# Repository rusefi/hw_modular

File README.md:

This repo is abandoned because https://github.com/andreika-git/hellen-one is the way!

Home of rusEFI modular prototyping hardware

https://github.com/rusefi/rusefi

Depends on libraries from https://github.com/rusefi/kicad-libraries

If you download complete repo do not forget to download libraries. If you git clone be sure to also

`git submodule update --init`

# Modules

[Nucleo 144 Wings Base Board](NUCLEO144_wing)

[TLE8888 Base Chip](TLE8888_Module)

[Protected Analog Inputs](Analog_Input_Module)

[6 channel Hi-Side Driver](highside_module)

[14 channel Low-Side Driver](lowside)

[TLE7209 H-Bridge](TLE7209_or_MC33186_H-Bridge_Breakout)

[Wideband Sense CJ125](cj125_Module)

# See also

[Forum thread](https://rusefi.com/forum/viewtopic.php?f=4&t=1459)

If you download complete repo do not forget to download libraries. If you git clone be sure to also

`git submodule update --init`

See [Manhattan Standard](Manhattan_standard.md)

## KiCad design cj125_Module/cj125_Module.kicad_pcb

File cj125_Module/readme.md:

See also https://github.com/rusefi/rusefi/wiki/WBO
 
[iBom](https://rusefi.com/docs/ibom/cj125_Module_latest.html)

on this board UR does NOT have build-in resistor divider

on this board UA resistor divider with 1.68 ratio

| Module Pin  | Sensor wire  |
|---|---|
| HT1  | H+ constant +12v  |
| GATE  | H- low side heater control  |
| VM1  |  VS/IP=VM=common virtual ground for VS and IP |
| IP1   | IP  |
| UN1  | VS pin 6, black  |
| IA1  |  CalR  pin 5, green |

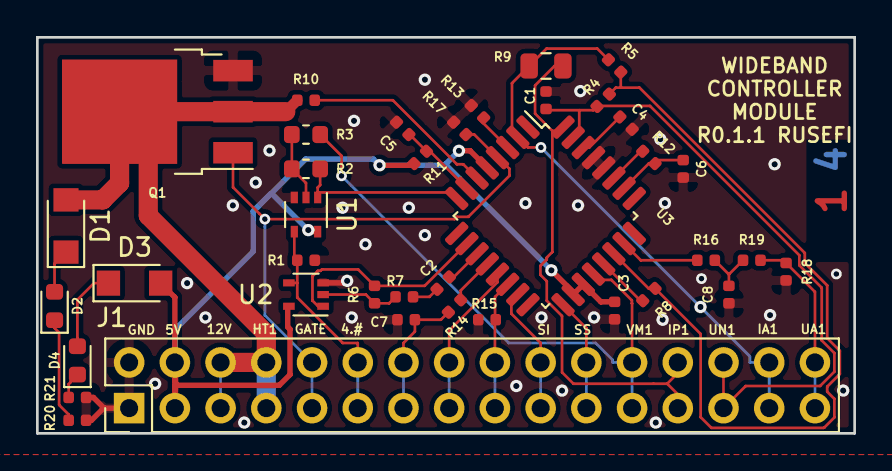
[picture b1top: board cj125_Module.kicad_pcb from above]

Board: 2 copper layers, 45.4 x 22.0 mm, 38 parts (0 on the bottom side), 36 nets.

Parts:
C1: 220pf; C_0402_1005Metric
C2, C6: 100nF; C_0402_1005Metric
C3, C4, C7, C8: 33nF; C_0402_1005Metric
C5: 1nF; C_0402_1005Metric
D1, D3: D_Schottky; D_SMF
D2, D4: LED; LED_0603_1608Metric
J1: Conn_02x20_Odd_Even; PinHeader_2x16_P2.54mm_Vertical
Q1: buk 100-50; TO-252-3_TabPin2
R1, R7: 10K; R_0402_1005Metric
R2: 220R; R_0603_1608Metric
R3: 82.5R; R_0603_1608Metric
R4, R12, R15: 100K; R_0402_1005Metric
R5: 470K; R_0402_1005Metric
R6: 21.6K; R_0402_1005Metric
R8, R20: 4.7K; R_0402_1005Metric
R9: 61.9R; R_0805_2012Metric
R10, R19: 6.8K; R_0402_1005Metric
R11, R13, R17, R18: 10k; R_0402_1005Metric
R14, R16, R21: 1K; R_0402_1005Metric
U1, U2: TS5A3166DCKR; SOT-353_SC-70-5
U3: CJ125; LQFP-32_7x7mm_P0.8mm

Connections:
/4.2_4.9: J1.11, J1.12, R1.2, U1.4, U2.4
/5V: C3.2, D3.2, J1.3, J1.4, R11.2, U1.5, U2.5, U3.5, U3.18, U3.19
/CJ125-1-SCK: J1.15, J1.16, U3.13
/CJ125-1-SI: J1.19, J1.20, U3.15
/CJ125-1-SO: J1.17, J1.18, R15.2, U3.14
/CJ125-1-SS: J1.21, J1.22, U3.17
/CJ125-UA-1: J1.31, J1.32, R18.1, R19.1
/CJ125_HEATER-1: D1.2, J1.5, J1.6, J1.7, J1.8, Q1.2, R10.1
/CJ125_UR-1: C7.1, J1.13, J1.14, R14.1
/COM: R2.1, R3.2, U1.2
/LSU-HEAT-GATE: J1.9, J1.10, Q1.1, R17.2, U3.4
/LSUIA1: J1.29, J1.30, R5.1, R9.1, U3.2
/LSUIP1: J1.25, J1.26, R9.2, U3.32
/LSUUN1: C1.1, J1.27, J1.28, R4.2, U3.31
/LSUVM1: J1.23, J1.24, R3.1, U3.20
/NO: R2.2, U1.1, U3.8
/WO2-12V: C4.2, U3.30
GND: C1.2, C3.1, C4.1, C5.2, C6.1, C7.2, C8.1, J1.1, J1.2, Q1.3, R1.1, R13.1, R15.1, R17.1, R18.2, R20.1, R21.1, U1.3, U2.3, U3.28, U3.29
unnamed: C2.1, R7.1
unnamed: C2.2, U3.11
unnamed: C5.1, R11.1, U3.7
unnamed: C6.2, R12.2, U3.26
unnamed: C8.2, R16.1, R19.2
unnamed: D1.1, D2.2
unnamed: D2.1, R20.2
unnamed: D3.1, D4.2
unnamed: D4.1, R21.2
unnamed: R4.1, R5.2, R8.1, U3.22
unnamed: R6.1, R7.2, U2.2
unnamed: R6.2, U2.1, U3.10
unnamed: R8.2, U3.21
unnamed: R10.2, U3.6
unnamed: R12.1, U3.27
unnamed: R13.2, U3.3
unnamed: R14.2, U3.12
unnamed: R16.2, U3.23

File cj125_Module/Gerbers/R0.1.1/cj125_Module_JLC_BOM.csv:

Comment,Designator,Footprint,LCSC, LCSC, Part #
"220pf","C1","Capacitor_SMD:C_0402_1005Metric","","C1530","C1530"
"33nF","C4,C7,C8,C3","Capacitor_SMD:C_0402_1005Metric",""," C1585"," C1585"
"1nF","C5","Capacitor_SMD:C_0402_1005Metric",""," C1523"," C1523"
"100nF","C6,C2","Capacitor_SMD:C_0402_1005Metric","","C1525","C1525"
"D_Schottky","D1,D3","Diode_SMD:D_SMF","","C64898",""
"LED","D2,D4","LED_SMD:LED_0603_1608Metric","","C2286",""
"Conn_02x20_Odd_Even","J1","Connector_PinHeader_2.54mm:PinHeader_2x16_P2.54mm_Vertical",""
"buk 100-50","Q1","Package_TO_SOT_SMD:TO-252-3_TabPin2","","","512-RFD16N05LSM9A"
"6.8K","R10,R19","Resistor_SMD:R_0402_1005Metric","","C25917","C25917"
"10k","R11,R13,R17,R18","Resistor_SMD:R_0402_1005Metric","","C25744","C25744"
"100K","R12,R4,R15","Resistor_SMD:R_0402_1005Metric","","C25741","C25741"
"1K","R16,R14,R21","Resistor_SMD:R_0402_1005Metric","","C11702","C11702"
"220R","R2","Resistor_SMD:R_0603_1608Metric",""," C22962"," C22962"
"82.5R","R3","Resistor_SMD:R_0603_1608Metric","","C23117",""
"470K","R5","Resistor_SMD:R_0402_1005Metric","","C25790","C25790"
"21.6K","R6","Resistor_SMD:R_0402_1005Metric",""," C25872"," C22962"
"10K","R7,R1","Resistor_SMD:R_0402_1005Metric",""," C25744",""
"4.7K","R8,R20","Resistor_SMD:R_0402_1005Metric","","C25900","C25900"
"61.9R","R9","Resistor_SMD:R_0805_2012Metric","","C17778","C17778"
"TS5A3166DCKR","U1,U2","Package_TO_SOT_SMD:SOT-353_SC-70-5",""
"CJ125","U3","Package_QFP:LQFP-32_7x7mm_P0.8mm",""

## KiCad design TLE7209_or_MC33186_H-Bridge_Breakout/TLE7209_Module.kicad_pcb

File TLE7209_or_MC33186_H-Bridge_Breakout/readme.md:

22x43mm

[Forum Thread](https://rusefi.com/forum/viewtopic.php?f=4&t=1521)

2 layer (also 4 layer version? TODO: add some clarity)

iBom https://rusefi.com/docs/ibom/TLE7209_Module_latest.html

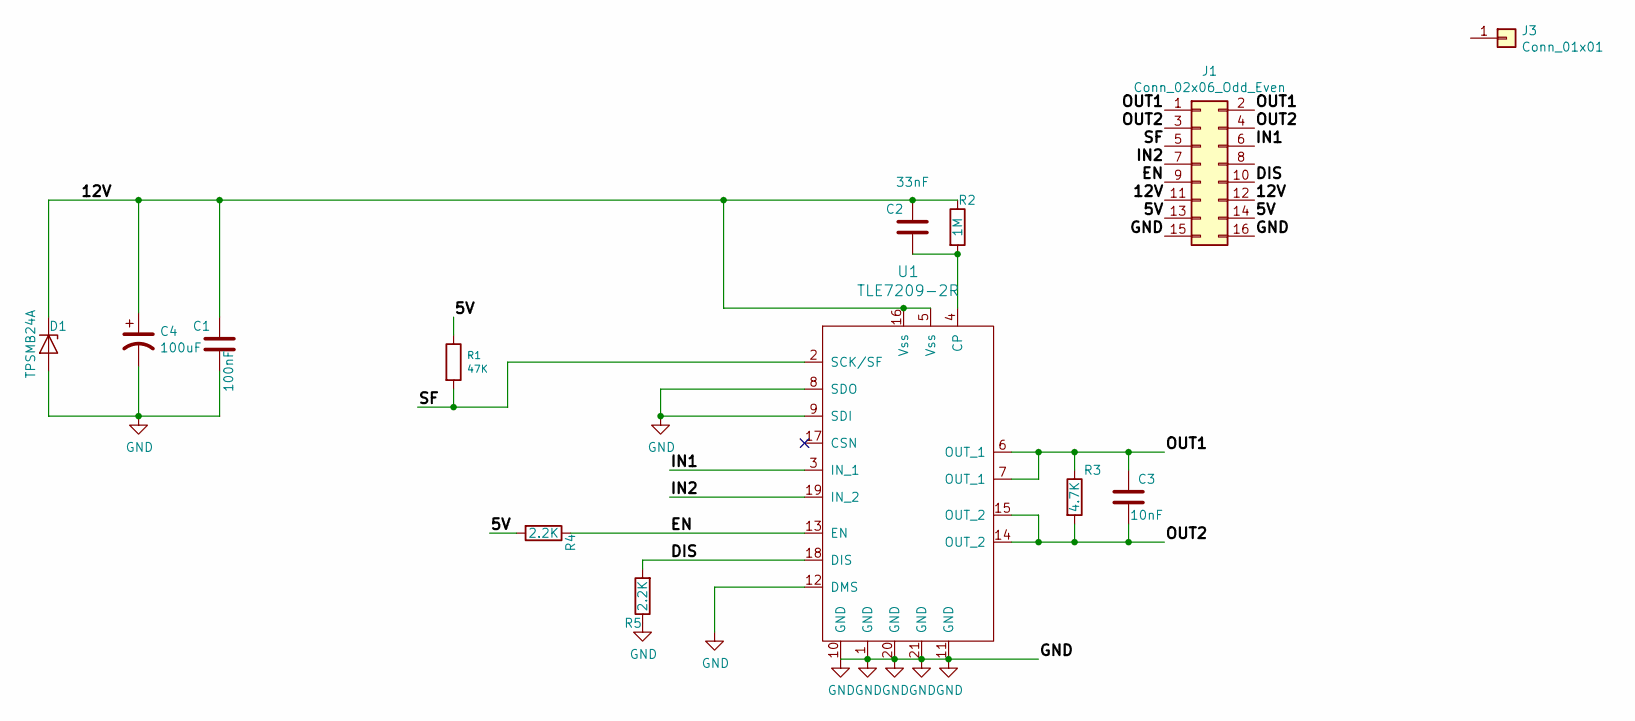
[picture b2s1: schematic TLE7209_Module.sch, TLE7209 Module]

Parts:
C1: 100nF; C_0805_2012Metric_Pad1.15x1.40mm_HandSolder
C2: 33nF; C_0805_2012Metric_Pad1.15x1.40mm_HandSolder
C3: 10nF; C_0805_2012Metric_Pad1.15x1.40mm_HandSolder
C4: 100uF; CP_Elec_8x10
D1: TPSMB24A; D_SMA
J1: Conn_02x06_Odd_Even; PinHeader_2x08_P2.54mm_Vertical
J3: Conn_01x01; 1pin
R1: 47K; R_0805_2012Metric_Pad1.15x1.40mm_HandSolder
R2: 1M; R_0805_2012Metric_Pad1.15x1.40mm_HandSolder
R3: 4.7K; R_0805_2012Metric_Pad1.15x1.40mm_HandSolder
R4, R5: 2.2K; R_0805_2012Metric_Pad1.15x1.40mm_HandSolder
U1: TLE7209-2R; HSOP-20-1EP_11.0x15.9mm_P1.27mm_SlugDown_ThermalVias

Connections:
/5V: J1.13, J1.14, R1.1, R4.2
/12V: C1.1, C2.1, C4.1, D1.1 (K), J1.11, J1.12, R2.1, U1.5 (Vss), U1.16 (Vss)
/DIS: J1.10, R5.2, U1.18 (DIS)
/EN: J1.9, R4.1, U1.13 (EN)
/IN1: J1.6, U1.3 (IN_1)
/IN2: J1.7, U1.19 (IN_2)
/OUT1: C3.1, J1.1, J1.2, R3.1, U1.6 (OUT_1), U1.7 (OUT_1)
/OUT2: C3.2, J1.3, J1.4, R3.2, U1.14 (OUT_2), U1.15 (OUT_2)
/SF: J1.5, R1.2, U1.2 (SCK/SF)
GND: C1.2, C4.2, D1.2 (A), J1.15, J1.16, R5.1, U1.1 (GND), U1.8 (SDO), U1.9 (SDI), U1.10 (GND), U1.11 (GND), U1.12 (DMS), U1.20 (GND), U1.21 (GND)
unnamed: C2.2, R2.2, U1.4 (CP)

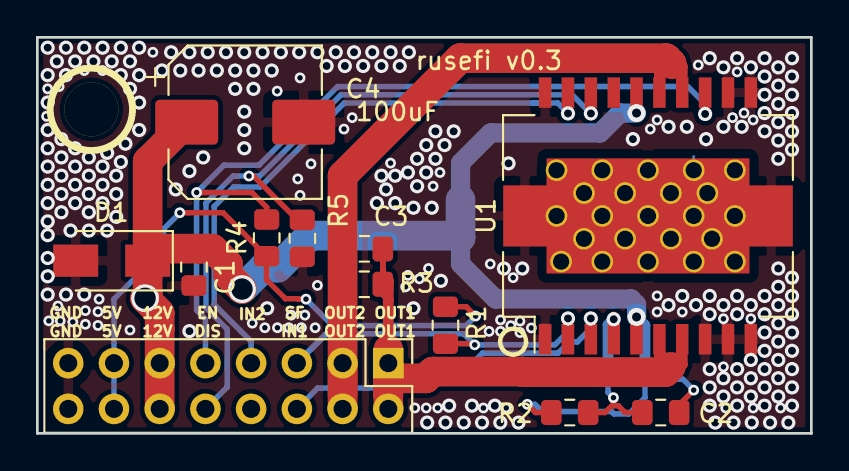
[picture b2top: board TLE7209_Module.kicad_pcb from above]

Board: 2 copper layers, 43.0 x 22.0 mm, 13 parts (0 on the bottom side), 11 nets.

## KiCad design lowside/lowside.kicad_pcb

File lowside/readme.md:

[iBOM](https://rusefi.com/docs/ibom/lowside_0.1.html)

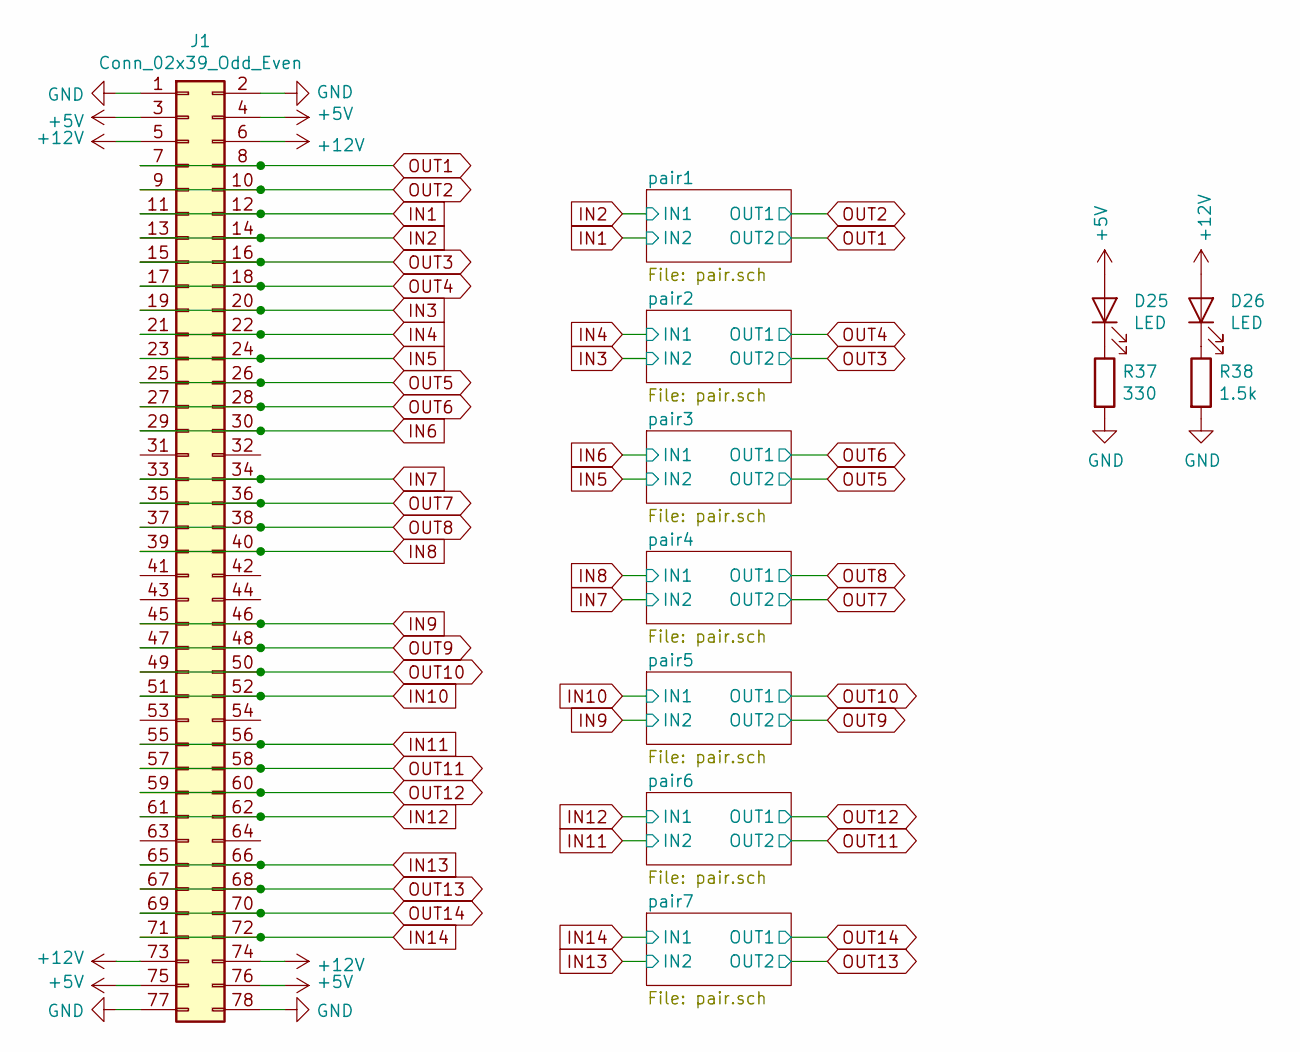
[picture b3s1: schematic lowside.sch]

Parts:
D25, D26: LED; LED_0603_1608Metric
J1: Conn_02x39_Odd_Even; PinHeader_2x39_P2.54mm_Vertical
R37: 330; R_0603_1608Metric
R38: 1.5k; R_0603_1608Metric

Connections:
+5V: D25.2 (A), J1.3, J1.4, J1.75, J1.76
+12V: D26.2 (A), J1.5, J1.6, J1.73, J1.74; also elsewhere on the board
GND: J1.1, J1.2, J1.77, J1.78, R37.2, R38.2; also elsewhere on the board
IN1: J1.11, J1.12; also elsewhere on the board
IN2: J1.13, J1.14; also elsewhere on the board
IN3: J1.19, J1.20; also elsewhere on the board
IN4: J1.21, J1.22; also elsewhere on the board
IN5: J1.23, J1.24; also elsewhere on the board
IN6: J1.29, J1.30; also elsewhere on the board
IN7: J1.33, J1.34; also elsewhere on the board
IN8: J1.39, J1.40; also elsewhere on the board
IN9: J1.45, J1.46; also elsewhere on the board
IN10: J1.51, J1.52; also elsewhere on the board
IN11: J1.55, J1.56; also elsewhere on the board
IN12: J1.61, J1.62; also elsewhere on the board
IN13: J1.65, J1.66; also elsewhere on the board
IN14: J1.71, J1.72; also elsewhere on the board
unnamed: D25.1 (K), R37.1
unnamed: D26.1 (K), R38.1
OUT3: J1.15, J1.16; also elsewhere on the board
OUT4: J1.17, J1.18; also elsewhere on the board
OUT5: J1.25, J1.26; also elsewhere on the board
OUT6: J1.27, J1.28; also elsewhere on the board
OUT9: J1.47, J1.48; also elsewhere on the board
OUT10: J1.49, J1.50; also elsewhere on the board
OUT11: J1.57, J1.58; also elsewhere on the board
OUT12: J1.59, J1.60; also elsewhere on the board
OUT13: J1.67, J1.68; also elsewhere on the board
OUT14: J1.69, J1.70; also elsewhere on the board

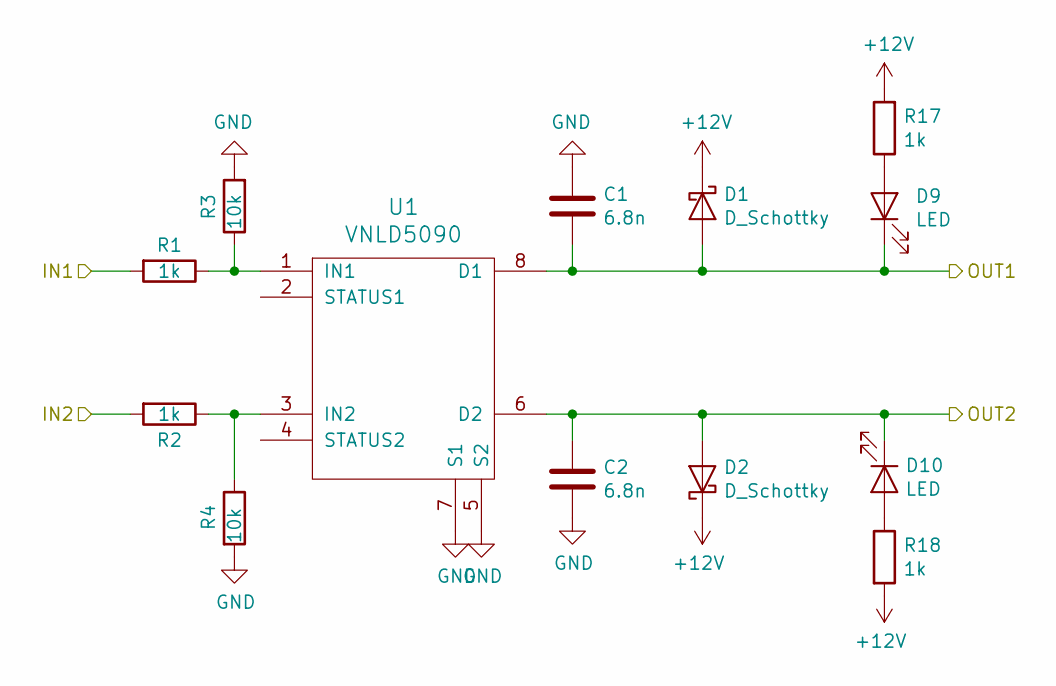
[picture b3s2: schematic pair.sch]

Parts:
C1, C2: 6.8n; C_0603_1608Metric
D1, D2: D_Schottky; D_SMF
D15, D16: LED; LED_0603_1608Metric
R1, R2, R23, R24: 1k; R_0603_1608Metric
R3, R4: 10k; R_0603_1608Metric
U1: VNLD5090; SO-8_3.9x4.9mm_P1.27mm

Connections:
+12V: D1.1 (K), D2.1 (K), R23.2, R24.2; also elsewhere on the board
GND: C1.2, C2.2, R3.2, R4.2, U1.5 (S2), U1.7 (S1); also elsewhere on the board
IN1: R2.2; also elsewhere on the board
IN2: R1.2; also elsewhere on the board
unnamed: D15.2 (A), R23.1
unnamed: D16.2 (A), R24.1
unnamed: R1.1, R3.1, U1.1 (IN1)
unnamed: R2.1, R4.1, U1.3 (IN2)

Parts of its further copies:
C3, C4, C5, C6, C7, C8, C9, C10, C11, C12, C13, C14: 6.8n; C_0603_1608Metric
D3, D4, D5, D6, D7, D8, D17, D18, D21, D22, D27, D28: D_Schottky; D_SMF
D9, D10, D11, D12, D13, D14, D19, D20, D23, D24, D29, D30: LED; LED_0603_1608Metric
R5, R6, R9, R10, R13, R14, R17, R18, R19, R20, R21, R22, R25, R26, R29, R30, R31, R32, R35, R36, R39, R40, R43, R44: 1k; R_0603_1608Metric
R7, R8, R11, R12, R15, R16, R27, R28, R33, R34, R41, R42: 10k; R_0603_1608Metric
U2, U3, U4, U5, U6, U7: VNLD5090; SO-8_3.9x4.9mm_P1.27mm

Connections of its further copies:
+12V: D3.1 (K), D4.1 (K), D5.1 (K), D6.1 (K), D7.1 (K), D8.1 (K), D17.1 (K), D18.1 (K), D21.1 (K), D22.1 (K), D27.1 (K), D28.1 (K), R17.2, R18.2, R19.2, R20.2, R21.2, R22.2, R29.2, R30.2, R35.2, R36.2, R43.2, R44.2; also elsewhere on the board
GND: C3.2, C4.2, C5.2, C6.2, C7.2, C8.2, C9.2, C10.2, C11.2, C12.2, C13.2, C14.2, R7.2, R8.2, R11.2, R12.2, R15.2, R16.2, R27.2, R28.2, R33.2, R34.2, R41.2, R42.2, U2.5 (S2), U2.7 (S1), U3.5 (S2), U3.7 (S1), U4.5 (S2), U4.7 (S1), U5.5 (S2), U5.7 (S1), U6.5 (S2), U6.7 (S1), U7.5 (S2), U7.7 (S1); also elsewhere on the board
IN3: R6.2; also elsewhere on the board
IN4: R5.2; also elsewhere on the board
IN5: R10.2; also elsewhere on the board
IN6: R9.2; also elsewhere on the board
IN7: R14.2; also elsewhere on the board
IN8: R13.2; also elsewhere on the board
IN9: R26.2; also elsewhere on the board
IN10: R25.2; also elsewhere on the board
IN11: R32.2; also elsewhere on the board
IN12: R31.2; also elsewhere on the board
IN13: R40.2; also elsewhere on the board
IN14: R39.2; also elsewhere on the board
unnamed: D9.2 (A), R17.1
unnamed: D10.2 (A), R18.1
unnamed: D11.2 (A), R19.1
unnamed: D12.2 (A), R20.1
unnamed: D13.2 (A), R21.1
unnamed: D14.2 (A), R22.1
unnamed: D19.2 (A), R29.1
unnamed: D20.2 (A), R30.1
unnamed: D23.2 (A), R35.1
unnamed: D24.2 (A), R36.1
unnamed: D29.2 (A), R43.1
unnamed: D30.2 (A), R44.1
unnamed: R5.1, R7.1, U2.1 (IN1)
unnamed: R6.1, R8.1, U2.3 (IN2)
unnamed: R10.1, R12.1, U3.3 (IN2)
unnamed: R9.1, R11.1, U3.1 (IN1)
unnamed: R13.1, R15.1, U4.1 (IN1)
unnamed: R14.1, R16.1, U4.3 (IN2)
unnamed: R25.1, R27.1, U5.1 (IN1)
unnamed: R26.1, R28.1, U5.3 (IN2)
unnamed: R31.1, R33.1, U6.1 (IN1)
unnamed: R32.1, R34.1, U6.3 (IN2)
unnamed: R39.1, R41.1, U7.1 (IN1)
unnamed: R40.1, R42.1, U7.3 (IN2)
OUT3: C4.1, D4.2 (A), D12.1 (K), U2.6 (D2); also elsewhere on the board
OUT4: C3.1, D3.2 (A), D11.1 (K), U2.8 (D1); also elsewhere on the board
OUT5: C6.1, D6.2 (A), D14.1 (K), U3.6 (D2); also elsewhere on the board
OUT6: C5.1, D5.2 (A), D13.1 (K), U3.8 (D1); also elsewhere on the board
OUT9: C10.1, D18.2 (A), D20.1 (K), U5.6 (D2); also elsewhere on the board
OUT10: C9.1, D17.2 (A), D19.1 (K), U5.8 (D1); also elsewhere on the board
OUT11: C12.1, D22.2 (A), D24.1 (K), U6.6 (D2); also elsewhere on the board
OUT12: C11.1, D21.2 (A), D23.1 (K), U6.8 (D1); also elsewhere on the board
OUT13: C14.1, D28.2 (A), D30.1 (K), U7.6 (D2); also elsewhere on the board
OUT14: C13.1, D27.2 (A), D29.1 (K), U7.8 (D1); also elsewhere on the board

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
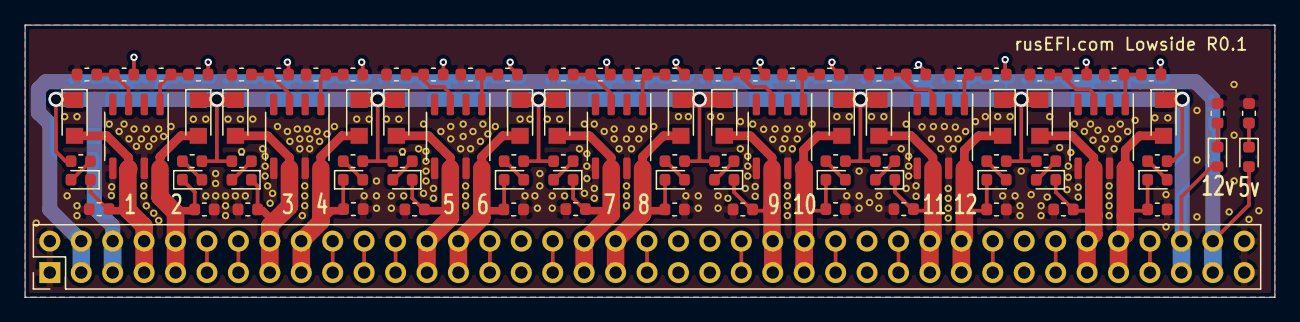
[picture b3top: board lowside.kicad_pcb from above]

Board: 4 copper layers, 101.0 x 22.0 mm, 96 parts (0 on the bottom side), 61 nets.

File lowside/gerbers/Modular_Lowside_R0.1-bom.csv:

Comment,Designator,Footprint,LCSC Part #
"6.8n",C1 C2 C3 C4 C5 C6 C7 C8 C9 C10 C11 C12 C13 C14 ,"Capacitor_SMD:C_0603_1608Metric","C1631"
"D_Schottky",D1 D2 D3 D4 D5 D6 D7 D8 D17 D18 D21 D22 D27 D28 ,"Diode_SMD:D_SMF","C156309"
"LED",D25 D26 D10 D9 D12 D11 D14 D13 D16 D15 D20 D19 D24 D23 D30 D29 ,"LED_SMD:LED_0603_1608Metric","C2286"
"Conn_02x39_Odd_Even",J1 ,"Connector_PinHeader_2.54mm:PinHeader_2x39_P2.54mm_Vertical",
"1k",R1 R2 R18 R17 R5 R6 R20 R19 R9 R10 R22 R21 R13 R14 R24 R23 R25 R26 R30 R29 R31 R32 R36 R35 R39 R40 R44 R43 ,"Resistor_SMD:R_0603_1608Metric","C21190"
"330",R37 ,"Resistor_SMD:R_0603_1608Metric","C23025"
"1.5k",R38 ,"Resistor_SMD:R_0603_1608Metric","C25867"
"10k",R4 R3 R8 R7 R12 R11 R16 R15 R28 R27 R34 R33 R42 R41 ,"Resistor_SMD:R_0603_1608Metric","C25804"
"VNLD5090",U1 U2 U3 U4 U5 U6 U7 ,"Package_SO:SO-8_3.9x4.9mm_P1.27mm","C377942"

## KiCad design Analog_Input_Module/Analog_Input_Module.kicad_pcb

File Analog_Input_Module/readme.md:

iBom https://rusefi.com/docs/ibom/Analog_Input_Module_latest.html

```
 1) RESOLVED IN R0.2     wrong diode symbol

```

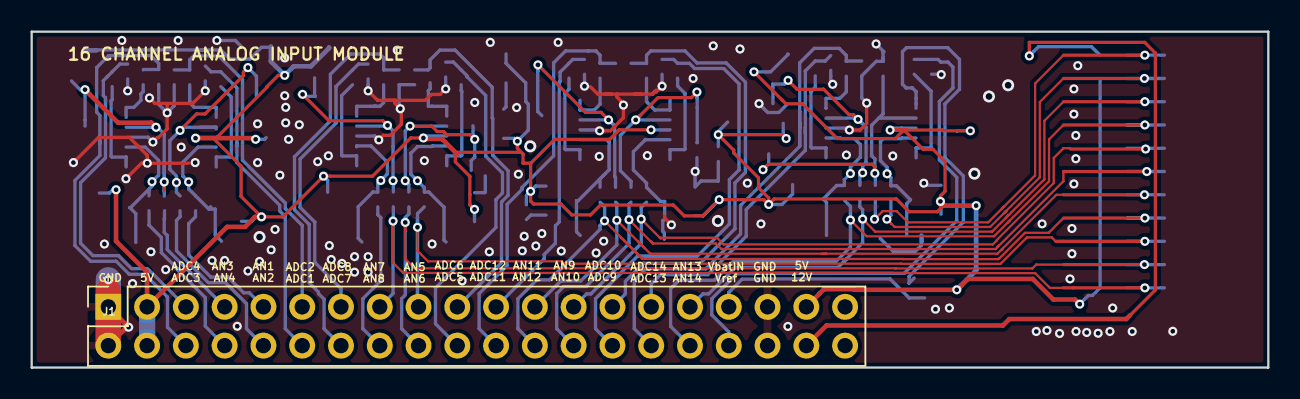
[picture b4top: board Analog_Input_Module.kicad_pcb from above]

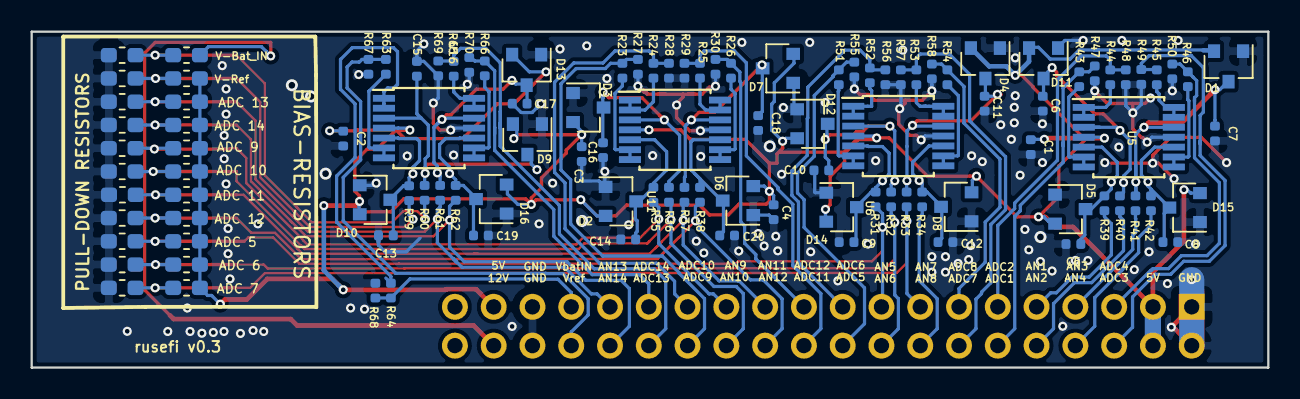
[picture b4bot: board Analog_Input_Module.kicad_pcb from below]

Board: 2 copper layers, 81.0 x 22.0 mm, 111 parts (110 on the bottom side), 67 nets.

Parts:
C1, C2, C3, C4: 100nF; C_0402_1005Metric
C5, C6, C7, C8, C9, C10, C11, C12, C13, C14, C15, C16, C17, C18, C19, C20: 10nF; C_0402_1005Metric
D1, D2, D3, D4, D5, D6, D7, D8, D9, D10, D11, D12, D13, D14, D15, D16: BAS70-04FILM; SOT-23
J1: Conn_02x20_Odd_Even; PinSocket_2x20_P2.54mm_Vertical
R1, R2, R5, R7, R9, R11, R17, R19, R20: DNP; R_0603_1608Metric_Pad1.05x0.95mm_HandSolder
R3, R4, R6, R8, R10, R13, R14, R18, R21, R22: 500K; R_0603_1608Metric_Pad1.05x0.95mm_HandSolder
R12: 1K; R_0603_1608Metric_Pad1.05x0.95mm_HandSolder
R15: 39K; R_0603_1608Metric_Pad1.05x0.95mm_HandSolder
R16: 10K; R_0603_1608Metric_Pad1.05x0.95mm_HandSolder
R23, R24, R25, R26, R43, R44, R45, R46, R51, R52, R53, R54, R63, R64, R65, R66: 1.5K; C_0402_1005Metric
R27, R28, R29, R30, R47, R48, R49, R50, R55, R56, R57, R58, R67, R68, R69, R70: 1K; C_0402_1005Metric
R31, R32, R33, R34, R35, R36, R37, R38, R39, R40, R41, R42, R59, R60, R61, R62: 10K; C_0402_1005Metric
U5, U6, U11, U16: MCP6004; TSSOP-14_4.4x5mm_P0.65mm

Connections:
/5V: C1.1, C2.1, C3.1, C4.1, D1.2, D2.2, D3.2, D4.2, D5.2, D6.2, D7.2, D8.2, D9.2, D10.2, D11.2, D12.2, D13.2, D14.2, D15.2, D16.2, J1.3, J1.4, J1.37, R1.2, R2.2, R5.2, R7.2, R9.2, R11.2, R12.2, R17.2, R19.2, R20.2, U5.4, U6.4, U11.4, U16.4
/ADC_1: J1.9, R39.2
/ADC_1_MCU: J1.12, R43.1, R47.2
/ADC_2: J1.10, R40.2
/ADC_2_MCU: J1.11, R44.1, R48.2
/ADC_3: J1.7, R41.2
/ADC_3_MCU: J1.6, R45.1, R49.2
/ADC_4: J1.8, R42.2
/ADC_4_MCU: J1.5, R46.1, R50.2
/ADC_5: J1.17, R7.1, R8.1, R31.2
/ADC_5_MCU: J1.20, R51.1, R55.2
/ADC_6: J1.18, R5.1, R6.1, R32.2
/ADC_6_MCU: J1.19, R52.1, R56.2
/ADC_7: J1.15, R1.1, R3.1, R33.2
/ADC_7_MCU: J1.14, R53.1, R57.2
/ADC_8: J1.16, R34.2
/ADC_8_MCU: J1.13, R54.1, R58.2
/ADC_9: J1.25, R19.1, R21.1, R35.2
/ADC_9_MCU: J1.28, R23.1, R27.2
/ADC_10: J1.26, R9.1, R10.1, R36.2
/ADC_10_MCU: J1.27, R24.1, R28.2
/ADC_11: J1.23, R2.1, R4.1, R37.2
/ADC_11_MCU: J1.22, R25.1, R29.2
/ADC_12: J1.24, R11.1, R13.1, R38.2
/ADC_12_MCU: J1.21, R26.1, R30.2
/ADC_13: J1.31, R17.1, R18.1, R61.2
/ADC_13_MCU: J1.30, R65.1, R69.2
/ADC_14: J1.32, R20.1, R22.1, R62.2
/ADC_14_MCU: J1.29, R66.1, R70.2
/U-Batt: J1.38, R15.2
/U-Batt_MCU: J1.33, R64.1, R68.2
/Vref: J1.34, R63.1, R67.2
GND: C1.2, C2.2, C3.2, C4.2, C5.2, C6.2, C7.2, C8.2, C9.2, C10.2, C11.2, C12.2, C13.2, C14.2, C15.2, C16.2, C17.2, C18.2, C19.2, C20.2, D1.1, D2.1, D3.1, D4.1, D5.1, D6.1, D7.1, D8.1, D9.1, D10.1, D11.1, D12.1, D13.1, D14.1, D15.1, D16.1, J1.1, J1.2, J1.35, J1.36, R3.2, R4.2, R6.2, R8.2, R10.2, R13.2, R14.2, R16.2, R18.2, R21.2, R22.2, R27.1, R28.1, R29.1, R30.1, R47.1, R48.1, R49.1, R50.1, R55.1, R56.1, R57.1, R58.1, R67.1, R68.1, R69.1, R70.1, U5.11, U6.11, U11.11, U16.11
unnamed: C5.1, D5.3, R39.1, U5.5
unnamed: C6.1, D11.3, R40.1, U5.3
unnamed: C7.1, D1.3, R41.1, U5.12
unnamed: C8.1, D15.3, R42.1, U5.10
unnamed: C9.1, D14.3, R31.1, U6.5
unnamed: C10.1, D12.3, R32.1, U6.3
unnamed: C11.1, D4.3, R33.1, U6.12
unnamed: C12.1, D8.3, R34.1, U6.10
unnamed: C13.1, D10.3, R59.1, U16.5
unnamed: C14.1, D2.3, R35.1, U11.5
unnamed: C15.1, D9.3, R60.1, U16.3
unnamed: C16.1, D3.3, R36.1, U11.3
unnamed: C17.1, D13.3, R61.1, U16.12
unnamed: C18.1, D7.3, R37.1, U11.12
unnamed: C19.1, D16.3, R62.1, U16.10
unnamed: C20.1, D6.3, R38.1, U11.10
unnamed: R12.1, R14.1, R59.2
unnamed: R15.1, R16.1, R60.2
unnamed: R23.2, U11.6, U11.7
unnamed: R24.2, U11.1, U11.2
unnamed: R25.2, U11.13, U11.14
unnamed: R26.2, U11.8, U11.9
unnamed: R43.2, U5.6, U5.7
unnamed: R44.2, U5.1, U5.2
unnamed: R45.2, U5.13, U5.14
unnamed: R46.2, U5.8, U5.9
unnamed: R51.2, U6.6, U6.7
unnamed: R52.2, U6.1, U6.2
unnamed: R53.2, U6.13, U6.14
unnamed: R54.2, U6.8, U6.9
unnamed: R63.2, U16.6, U16.7
unnamed: R64.2, U16.1, U16.2
unnamed: R65.2, U16.13, U16.14
unnamed: R66.2, U16.8, U16.9

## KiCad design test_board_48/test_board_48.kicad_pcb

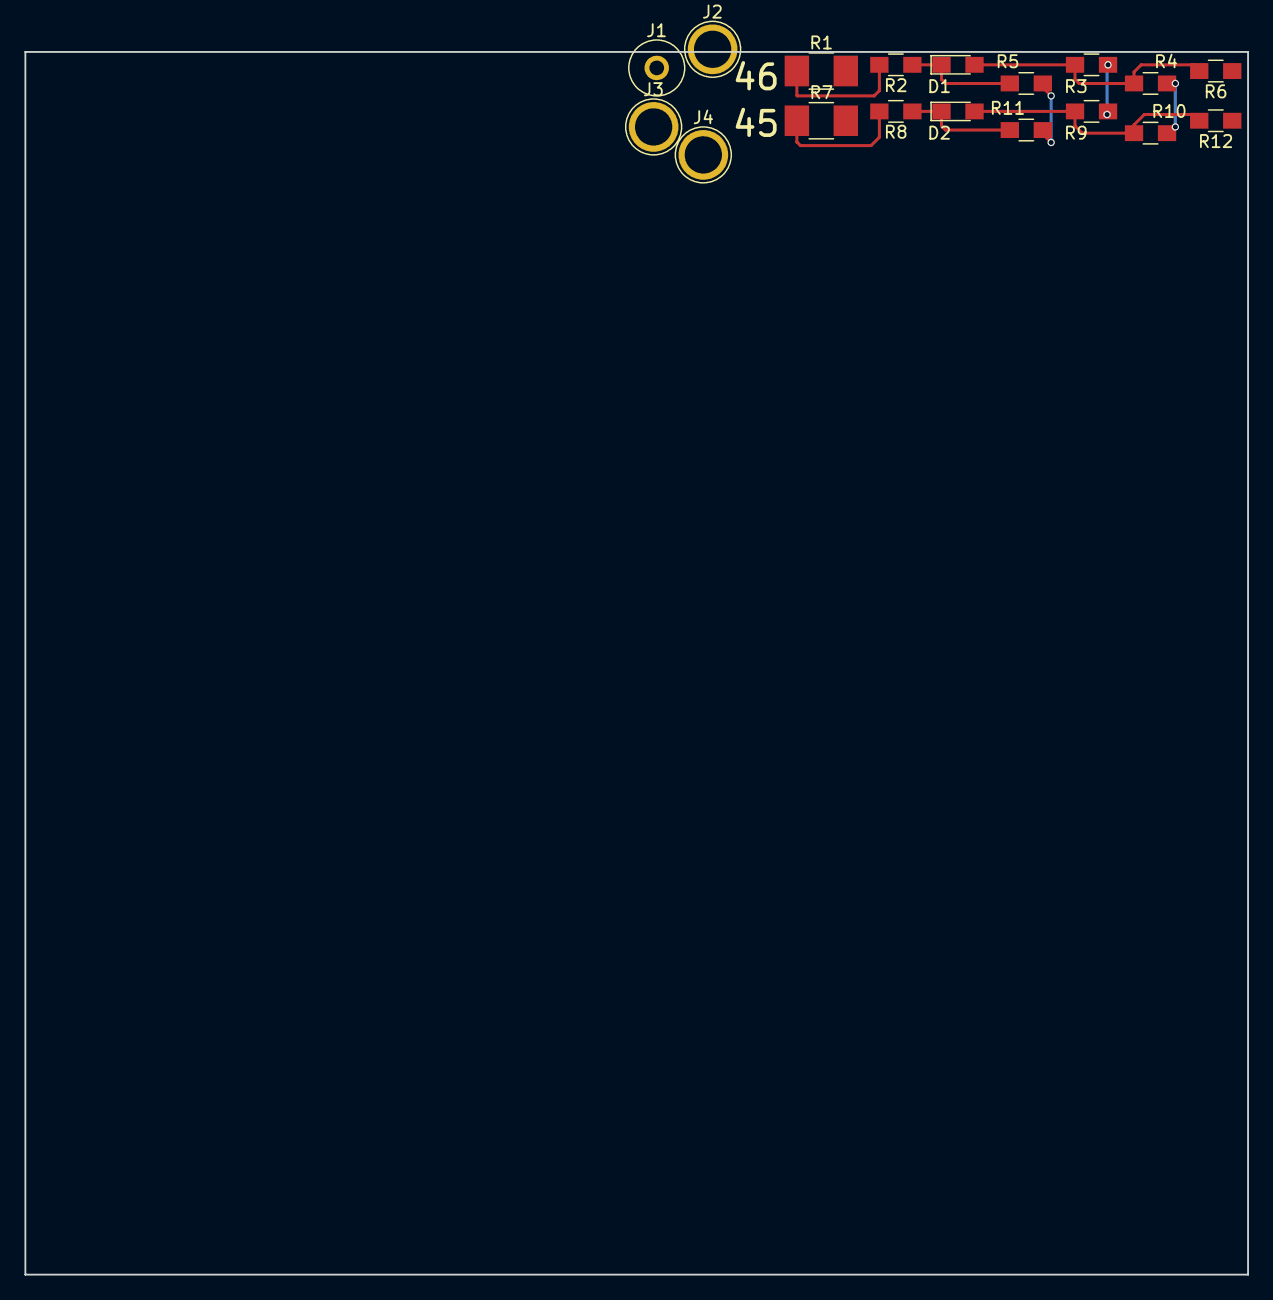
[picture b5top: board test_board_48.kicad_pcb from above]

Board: 2 copper layers, 100.0 x 100.0 mm, 18 parts (0 on the bottom side), 9 nets.

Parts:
D1, D2: LED; LED_0805_HandSoldering
J1, J2, J3, J4: Conn_01x01; 1pin
R1, R7: R; R_1210_HandSoldering
R2, R3, R4, R5, R6, R8, R9, R10, R11, R12: R; R_0805_HandSoldering

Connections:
/5v: R3.2, R9.2
/12v: R4.2, R10.2
GND: R1.2, R5.1, R6.1, R7.2, R11.1, R12.1
unnamed: D1.1, R2.1, R5.2
unnamed: D1.2, R3.1, R4.1, R6.2
unnamed: D2.1, R8.1, R11.2
unnamed: D2.2, R9.1, R10.1, R12.2
unnamed: J1.1, J2.1, R1.1, R2.2
unnamed: J3.1, J4.1, R7.1, R8.2

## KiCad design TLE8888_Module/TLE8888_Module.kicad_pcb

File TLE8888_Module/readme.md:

iBom https://rusefi.com/docs/ibom/TLE8888_Module_latest.html

[Forum thread](https://rusefi.com/forum/viewtopic.php?f=4&t=1496)

Brief overview of functionality

12v input: single input

5v output: build-in linear regulator

vdd input: logic level voltage from MCU used as reference to SPI etc communication

Open collector hall configurations:
DNP=R9=R15=R16=C12=C15. R17=2.7K R12=10K 
R13=0R R18=2.7K R19=2.7K

Validation: R(VR_IN_2, GND

```
Known issues:
  1)    fixed in 0.2      R25, R28, R14, R34 pull up LEDs up on TTL signals
```

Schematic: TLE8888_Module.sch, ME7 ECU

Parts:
C1, C4, C5, C6, C10, C13, C14, C16: 100nF; C_0603_1608Metric_Pad1.05x0.95mm_HandSolder
C2: 100UF 50V; CP_Elec_10x10.5; Part # UCD1H101MNL1GS
C3, C11: 4.7nF; C_0603_1608Metric_Pad1.05x0.95mm_HandSolder
C7, C8, C9: 10uF; C_0603_1608Metric_Pad1.05x0.95mm_HandSolder
C12, C15: DNP; C_0603_1608Metric_Pad1.05x0.95mm_HandSolder
D1: MBRS3200T3G; D_SMB; Part # MBRS3200T3G
D2: PESD1CAN-UX; SOT-323_SC-70_Handsoldering; Part # PESD1CANUX
D3, D4, D5, D7, D8, D9, D10, D11, D13, D14, D15, D16, D17: LED; LED_0603_1608Metric_Pad1.05x0.95mm_HandSolder
J1: DNP CORNER HOLE; 1pin
J2: Conn_02x39_Odd_Even; Conn_TLE8888_Module
J3: Conn_02x04_Odd_Even; PinHeader_2x04_P2.54mm_Vertical
Q1: IPD30N06S2L-23; TO-252-2; Part # IPD30N06S2L23AT3
R1, R11, R14, R24, R25, R26, R27, R28, R30, R31, R32, R33, R34: 1K; R_0603_1608Metric_Pad1.05x0.95mm_HandSolder
R2, R3, R4, R8, R10: 4.7K; R_0603_1608Metric_Pad1.05x0.95mm_HandSolder
R5, R6, R7: 0; R_0603_1608Metric_Pad1.05x0.95mm_HandSolder
R9, R12, R13, R15, R16, R17, R18, R19: DNP; R_0603_1608Metric_Pad1.05x0.95mm_HandSolder
R20, R21: 2.7K; R_0603_1608Metric_Pad1.05x0.95mm_HandSolder
R22: 120R; R_0603_1608Metric_Pad1.05x0.95mm_HandSolder
R23: TLE8888 LOGO DNP; TLE8888
U2: TLE8888QK; LQFP-100_14x14mm_P0.5mm_THERMAL; Part # TLE88882QKXUMA1

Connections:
/5V1: C4.1, J2.53, U2.9
/5V2: C5.1, J2.54, U2.10
/12V: C1.1, C2.1, C3.1, C16.1, D1.2 (A), D16.2 (A), J2.61, J2.62, R20.2, R21.2, U2.54, U2.87, U2.90
/CAN_H: D2.1, J3.2, R22.1, U2.46
/CAN_L: D2.2, J3.3, R22.2, U2.47
/CAN_RX: J3.6, U2.43
/CAN_TX: J3.5, U2.44
/CRNK+: C15.1, J2.60, R12.1, R15.1, R16.2, R17.2
/CRNK-: C15.2, J2.59, R13.1, R15.2, R18.2, R19.2
/CRNK_MCU: D17.2 (A), J2.58, U2.21
/CSN: J2.49, U2.3
/DFB_8: D14.1 (K), J2.28, U2.69
/DFB_9: J2.27, U2.70
/DFB_10: J2.29, U2.73
/DFB_11: J2.33, U2.76
/DFB_12: J2.40, U2.78
/DFB_13: J2.38, U2.80
/FCLP: J2.52, U2.7
/IGN_EN: R10.2, U2.27
/IGN_IN_1: D11.2 (A), J2.10, U2.32
/IGN_IN_2: J2.11, U2.33
/IGN_IN_3: J2.12, U2.34
/IGN_IN_4: J2.13, U2.35
/IGN_OUT_1: D5.2 (A), J2.45, U2.96
/IGN_OUT_2: J2.46, U2.97
/IGN_OUT_3: J2.47, U2.98
/IGN_OUT_4: J2.48, U2.99
/INJ_EN: R8.2, U2.24
/INJ_IN_1: D8.2 (A), J2.6, U2.28
/INJ_IN_2: J2.7, U2.29
/INJ_IN_3: J2.8, U2.30
/INJ_IN_4: J2.9, U2.31
/IN_9: J2.14, U2.36
/IN_10: J2.15, U2.37
/IN_11: J2.16, U2.38
/IN_12: J2.17, U2.39
/KEY: R5.2, U2.49
/LIN_IO: J3.4, U2.82
/LIN_RX: J3.8, U2.23
/LIN_TX: J3.7, U2.22
/MAIN_RELAY: J3.1, U2.55
/OUT_1: D7.1 (K), J2.22, U2.59, U2.60
/OUT_2: J2.21, U2.61, U2.62
/OUT_3: J2.24, U2.63, U2.64
/OUT_4: J2.23, U2.65, U2.66
/OUT_5: D13.1 (K), J2.34, U2.83, U2.84, U2.85
/OUT_6: J2.36, U2.92, U2.93, U2.94
/OUT_7: J2.55, U2.14, U2.15, U2.16
/OUT_8: D9.1 (K), J2.32, U2.71
/OUT_9: J2.30, U2.72
/OUT_10: J2.31, U2.74
/OUT_11: J2.35, U2.77
/OUT_12: J2.37, U2.79
/OUT_13: J2.39, U2.81
/OUT_14: J2.26, U2.68
/OUT_15: J2.25, U2.67
/OUT_16: J2.19, U2.58
/OUT_17: J2.20, U2.57
/OUT_18: D4.1 (K), J2.18, U2.56
/OUT_19: J2.57, U2.18
/OUT_20: J2.56, U2.17
/OUT_21: D10.1 (K), J2.43, U2.91
/OUT_22: J2.44, U2.89
/OUT_23: J2.42, U2.88
/OUT_24: J2.41, U2.86
/SDO: J2.50, U2.4
/SIP: J2.51, U2.5
/V5V: C6.1, C7.1, D15.2 (A), J2.3, J2.4, J2.63, J2.64, R3.2, R11.2, R17.1, R18.1, R24.2, R26.2, R27.2, R30.2, R31.2, U2.11, U2.45
/VDD: D3.2 (A), J2.5, R2.2, R4.2, R7.1, R8.1, R10.1
/VDDIO: R7.2, U2.20
/WAKE: R6.2, U2.48
GND: C1.2, C2.2, C4.2, C5.2, C6.2, C7.2, C8.2, C9.2, C10.2, C11.2, C13.2, C14.2, C16.2, D2.3, J2.1, J2.2, J2.65, J2.66, R1.2, R6.1, R14.1, R16.1, R19.1, R21.1, R25.1, R28.1, R32.2, R33.2, R34.1, U2.6, U2.19, U2.25, U2.26, U2.40, U2.42, U2.50, U2.53, U2.75, U2.100, U2.101
unnamed: C3.2, U2.95
unnamed: C8.1, C9.1, C10.1, Q1.3 (S), U2.12
unnamed: C11.1, Q1.1 (G), U2.13
unnamed: C12.1, R9.1, R12.2, U2.52
unnamed: C12.2, R9.2, R13.2, U2.51
unnamed: C13.1, U2.41
unnamed: C14.1, R5.1, R20.1
unnamed: D1.1 (K), Q1.2 (D)
unnamed: D3.1 (K), R1.1
unnamed: D4.2 (A), R11.1
unnamed: D5.1 (K), R14.2
unnamed: D7.2 (A), R24.1
unnamed: D8.1 (K), R25.2
unnamed: D9.2 (A), R26.1
unnamed: D10.2 (A), R27.1
unnamed: D11.1 (K), R28.2
unnamed: D13.2 (A), R30.1
unnamed: D14.2 (A), R31.1
unnamed: D15.1 (K), R32.1
unnamed: D16.1 (K), R33.1
unnamed: D17.1 (K), R34.2
unnamed: R2.1, U2.8
unnamed: R3.1, U2.2
unnamed: R4.1, U2.1

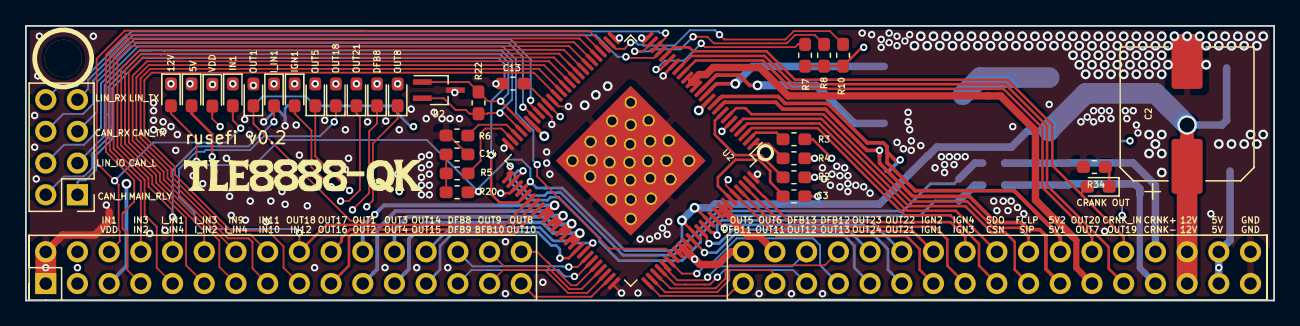
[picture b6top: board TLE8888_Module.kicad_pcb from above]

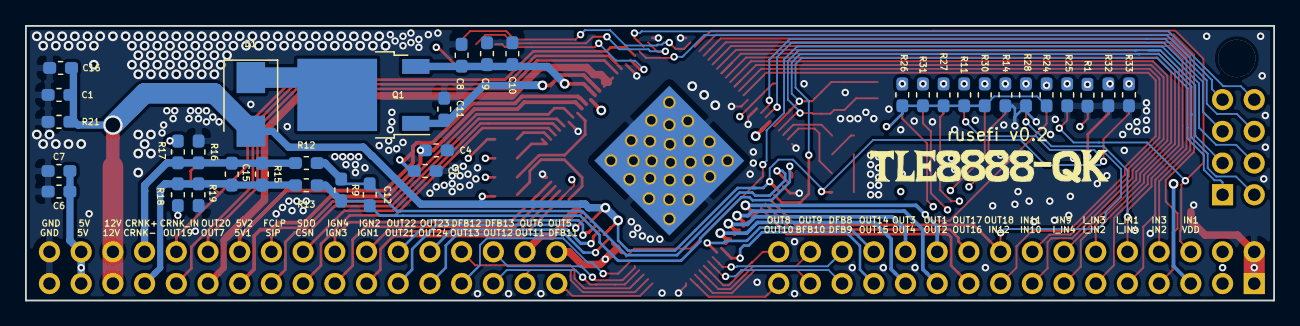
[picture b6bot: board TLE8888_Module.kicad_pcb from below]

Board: 4 copper layers, 100.0 x 22.0 mm, 70 parts (36 on the bottom side), 96 nets.

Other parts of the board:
R23#2: TLE8888 LOGO DNP; TLE8888

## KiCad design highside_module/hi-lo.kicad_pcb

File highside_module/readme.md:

Based on https://github.com/rusefi/rusefi/tree/master/hardware/hi-lo_driver

```
 1) ???? the part number is for SOIC package but the board has MSOP package. Part number should be TC4427AEUA
v 0.3 ordered on 03/12/2019
 2)                  fix 3D
```

iBom https://rusefi.com/docs/ibom/hi-lo_latest.html

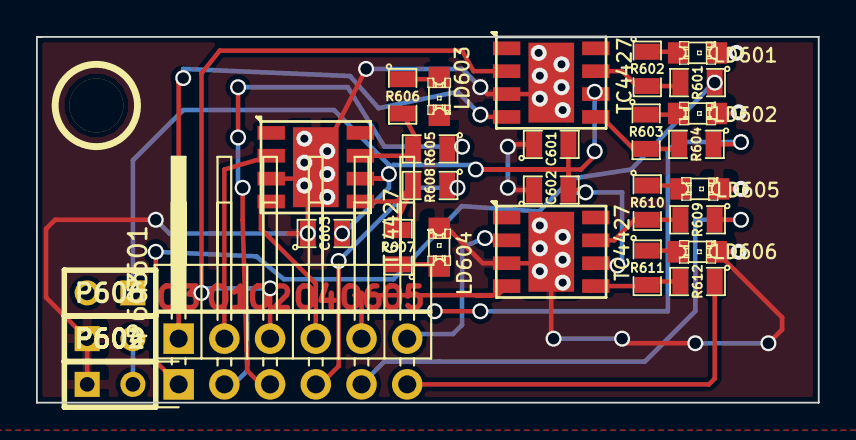
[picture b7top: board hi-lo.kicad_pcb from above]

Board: 2 copper layers, 43.4 x 20.3 mm, 31 parts (1 on the bottom side), 27 nets.

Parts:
C601, C602, C603: 0.1uF; SM0805
G601: LOGO; LOGO_F
LD601, LD602, LD603, LD604, LD605, LD606: LED; LED-0805
M601: CONN_1; 1pin
P601: CONN_3X2; Pin_Header_Angled_1x06_Pitch2.54mm
P602, P604, P606: CONN_2; SIL-2
P603: CONN_6; Pin_Header_Angled_1x06_Pitch2.54mm
R601, R604, R605, R608, R609, R612: 100; SM0805
R602, R603, R606, R607, R610, R611: 2700; SM0805
U601, U602, U603: TC4427; SOIC8-DFN

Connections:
5V: P602.2, P606.2
/HL1: P603.1, R601.1
/HL2: P603.2, R604.1
/HL3: P603.3, R605.1
/HL4: P603.4, R608.1
/HL5: P603.5, R609.1
/HL6: P603.6, R612.1
/H_IN1: P601.1, U601.4
/H_IN2: P601.2, U602.2
/H_IN3: P601.3, U601.2
/H_IN4: P601.4, U602.4
/H_IN5: P601.5, U603.4
/H_IN6: P601.6, U603.2
/VP: C601.2, C602.2, C603.2, P604.1, U601.6, U602.6, U603.6
GND: C601.1, C602.1, C603.1, LD601.2, LD602.2, LD603.2, LD604.2, LD605.2, LD606.2, P602.1, P606.1, U601.3, U601.9, U602.3, U602.9, U603.3, U603.9
unnamed: LD601.1, R602.1
unnamed: LD602.1, R603.1
unnamed: LD603.1, R606.1
unnamed: LD604.1, R607.1
unnamed: LD605.1, R610.1
unnamed: LD606.1, R611.1
unnamed: R601.2, R602.2, U601.7
unnamed: R603.2, R604.2, U601.5
unnamed: R605.2, R606.2, U602.7
unnamed: R607.2, R608.2, U602.5
unnamed: R609.2, R610.2, U603.7
unnamed: R611.2, R612.2, U603.5
